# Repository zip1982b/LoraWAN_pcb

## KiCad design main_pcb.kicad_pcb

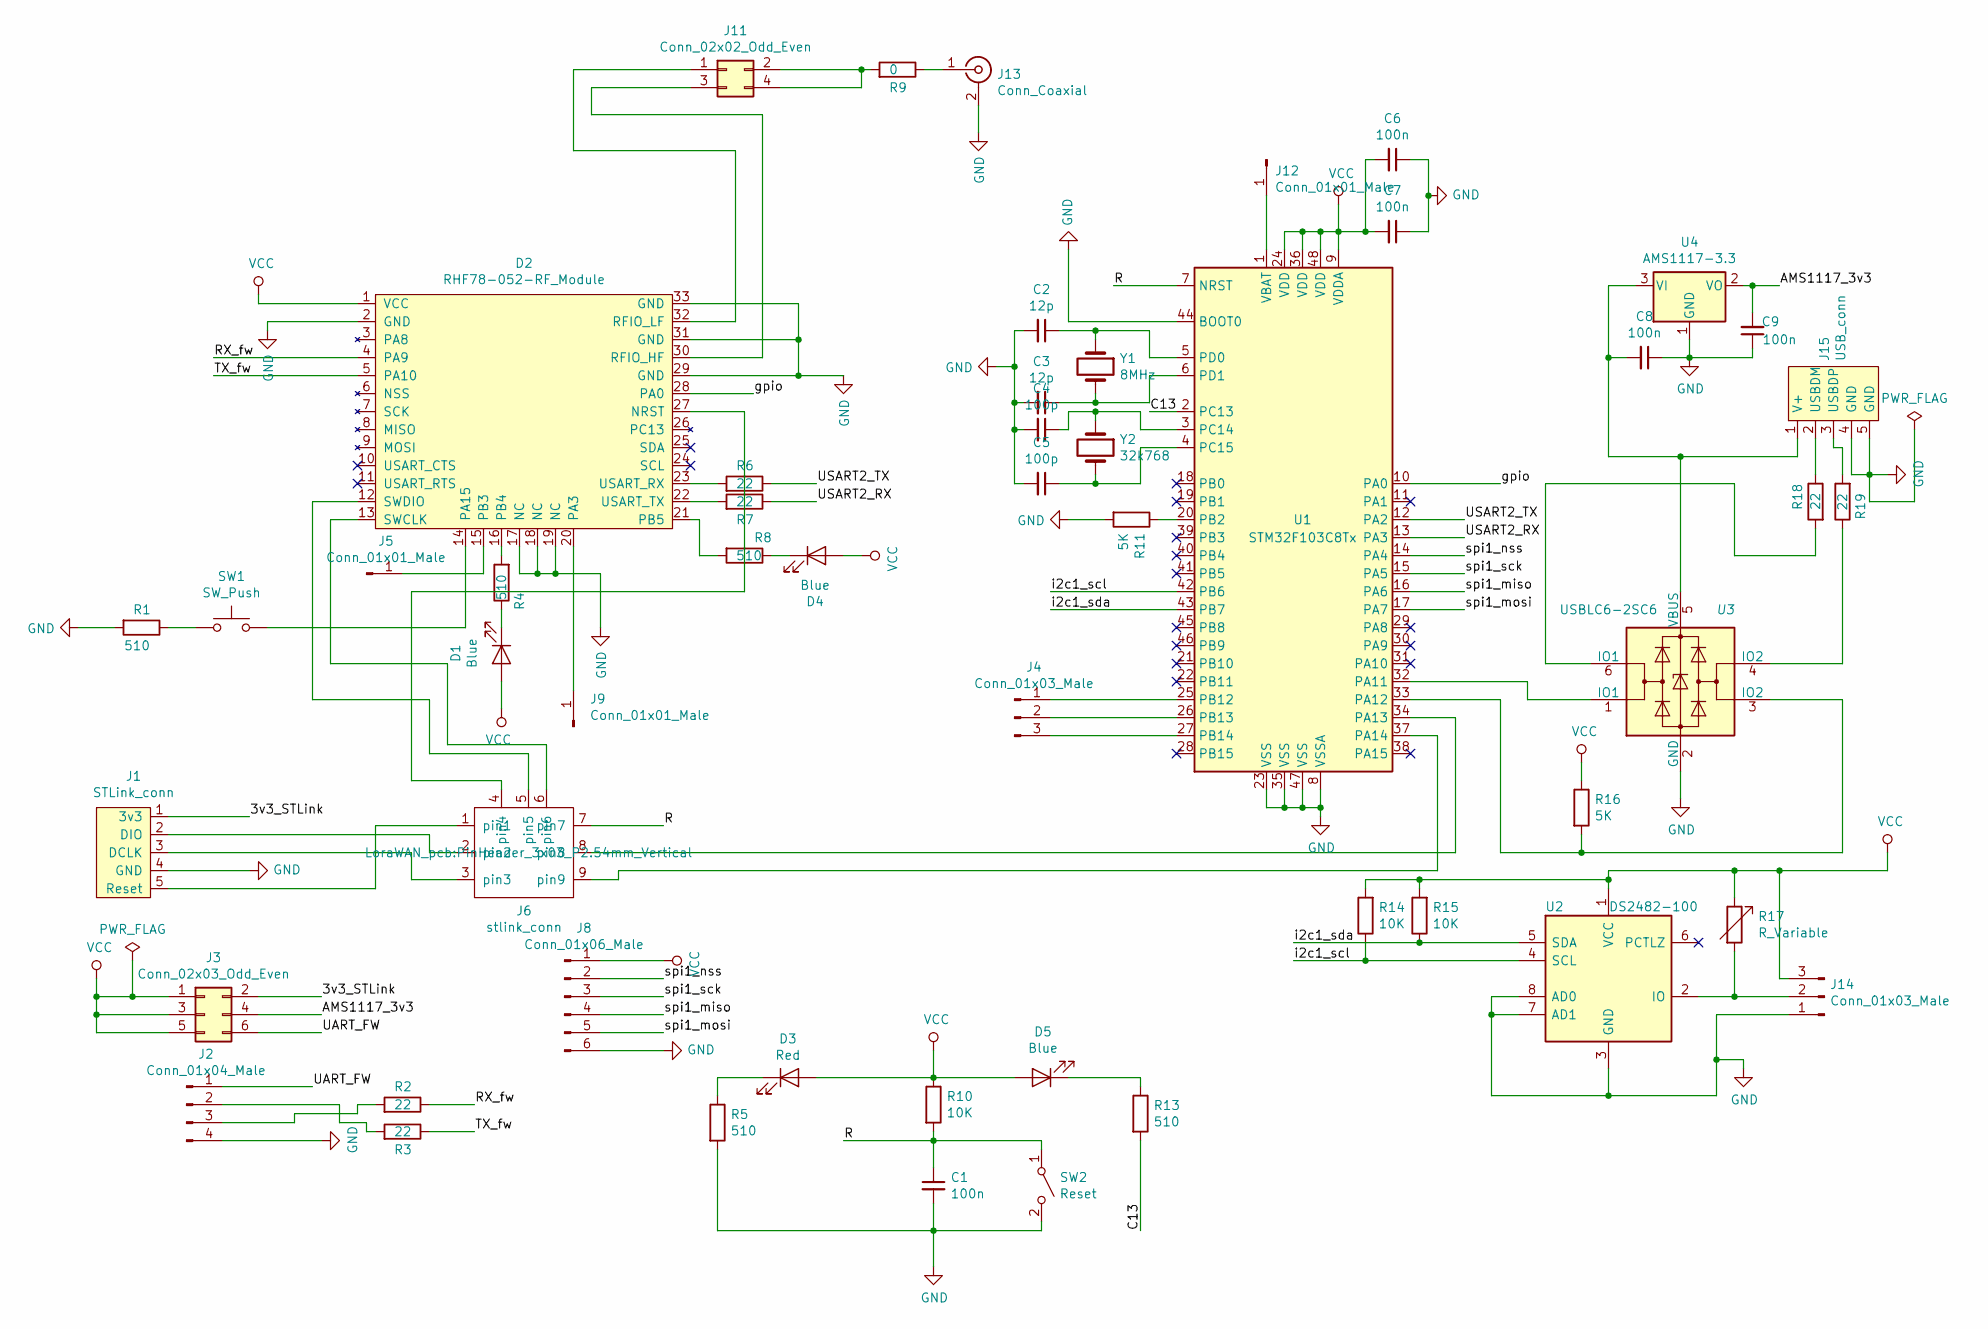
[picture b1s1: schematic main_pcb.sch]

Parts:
C1, C6, C7, C8, C9: 100n; C_0805_HandSoldering
C2, C3: 12p; C_0805_HandSoldering
C4, C5: 100p; C_0805_HandSoldering
D1, D4, D5: Blue; LED_0805_HandSoldering
D2: RHF78-052-RF_Module; RHF78_052
D3: Red; LED_0805_HandSoldering
J1: STLink_conn; Pin_Header_Straight_1x05_Pitch2.54mm
J2: Conn_01x04_Male; Pin_Header_Straight_1x04_Pitch2.54mm
J3: Conn_02x03_Odd_Even; Pin_Header_Straight_2x03_Pitch2.54mm
J4, J14: Conn_01x03_Male; Pin_Header_Straight_1x03_Pitch2.54mm
J5, J9, J12: Conn_01x01_Male; Pin_Header_Straight_1x01_Pitch2.54mm
J6: stlink_conn; PinHeader_3x03_P2.54mm_Vertical
J8: Conn_01x06_Male; Pin_Header_Straight_1x06_Pitch2.54mm
J11: Conn_02x02_Odd_Even; Pin_Header_Straight_2x02_Pitch2.54mm
J13: Conn_Coaxial; U_FL_smd
J15: USB_conn; USB_Micro-B
R1, R4, R5, R8, R13: 510; R_0805_HandSoldering
R2, R3, R6, R7, R18, R19: 22; R_0805_HandSoldering
R9: 0; R_0805_HandSoldering
R10, R14, R15: 10K; R_0805_HandSoldering
R11, R16: 5K; R_0805_HandSoldering
R17: R_Variable; Potentiometer_Trimmer_Bourns_3296W
SW1: SW_Push; SW_SPST_EVQPE1
SW2: Reset; SW_SPST_EVQPE1
U1: STM32F103C8Tx; LQFP-48_7x7mm_Pitch0.5mm
U2: DS2482-100; SOIC-8_3.9x4.9mm_Pitch1.27mm
U3: USBLC6-2SC6; SOT-23-6_Handsoldering
U4: AMS1117-3.3; SOT-223-3_TabPin2
Y1: 8MHz; Crystal_HC18-U_Vertical
Y2: 32k768; Crystal_AT310_d3.0mm_l10.0mm_Vertical

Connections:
/3v3_STLink: J1.1 (3v3), J3.2
/AMS1117_3v3: C9.2, J3.4, U4.2 (VO)
/C13: R13.2, U1.2 (PC13)
/R: C1.1, J6.7, R10.2, SW2.1 (A), U1.7 (NRST)
/RX_fw: D2.4 (PA9), R2.1
/TX_fw: D2.5 (PA10), R3.1
/UART_FW: J2.1, J3.6
/USART2_RX: R7.1, U1.13 (PA3)
/USART2_TX: R6.1, U1.12 (PA2)
/gpio: D2.28 (PA0), U1.10 (PA0)
/i2c1_scl: R14.1, U1.42 (PB6), U2.4 (SCL)
/i2c1_sda: R15.1, U1.43 (PB7), U2.5 (SDA)
/spi1_miso: J8.4, U1.16 (PA6)
/spi1_mosi: J8.5, U1.17 (PA7)
/spi1_nss: J8.2, U1.14 (PA4)
/spi1_sck: J8.3, U1.15 (PA5)
GND: C1.2, C2.2, C3.2, C4.2, C5.2, C6.1, C7.1, C8.1, C9.1, D2.2 (GND), D2.17 (NC), D2.18 (NC), D2.19 (NC), D2.29 (GND), D2.31 (GND), D2.33 (GND), J1.4 (GND), J2.4, J8.6, J13.2 (Ext), J14.1, J15.4 (GND), J15.5 (GND), R1.2, R5.2, R11.2, SW2.2 (B), U1.8 (VSSA), U1.23 (VSS), U1.35 (VSS), U1.44 (BOOT0), U1.47 (VSS), U2.3 (GND), U2.7 (AD1), U2.8 (AD0), U3.2 (GND), U4.1 (GND)
unnamed: C2.1, U1.5 (PD0), Y1.1
unnamed: C3.1, U1.6 (PD1), Y1.2
unnamed: C4.1, U1.3 (PC14), Y2.1
unnamed: C5.1, U1.4 (PC15), Y2.2
unnamed: C8.2, J15.1 (V+), U3.5 (VBUS), U4.3 (VI)
unnamed: D1.1 (K), R4.1
unnamed: D2.12 (SWDIO), J6.5
unnamed: D2.13 (SWCLK), J6.6
unnamed: D2.14 (PA15), SW1.2
unnamed: D2.15 (PB3), J5.1
unnamed: D2.16 (PB4), R4.2
unnamed: D2.20 (PA3), J9.1
unnamed: D2.21 (PB5), R8.2
unnamed: D2.22 (USART_TX), R7.2
unnamed: D2.23 (USART_RX), R6.2
unnamed: D2.27 (NRST), J6.4
unnamed: D2.30 (RFIO_HF), J11.3
unnamed: D2.32 (RFIO_LF), J11.1
unnamed: D3.1 (K), R5.1
unnamed: D4.1 (K), R8.1
unnamed: D5.1 (K), R13.1
unnamed: J1.2 (DIO), J6.2
unnamed: J1.3 (DCLK), J6.3
unnamed: J1.5 (Reset), J6.1
unnamed: J2.2, R3.2
unnamed: J2.3, R2.2
unnamed: J4.1, U1.25 (PB12)
unnamed: J4.2, U1.26 (PB13)
unnamed: J4.3, U1.27 (PB14)
unnamed: J6.8, U1.34 (PA13)
unnamed: J6.9, U1.37 (PA14)
unnamed: J11.2, J11.4, R9.2
unnamed: J12.1, U1.1 (VBAT)
unnamed: J13.1 (In), R9.1
unnamed: J14.2, R17.2, U2.2 (IO)
unnamed: J15.2 (USBDM), R18.1
unnamed: J15.3 (USBDP), R19.2
unnamed: R1.1, SW1.1
unnamed: R11.1, U1.20 (PB2)
unnamed: R16.2, U1.33 (PA12), U3.3 (IO2)
unnamed: R18.2, U3.6 (IO1)
unnamed: R19.1, U3.4 (IO2)
unnamed: U1.32 (PA11), U3.1 (IO1)
VCC: C6.2, C7.2, D1.2 (A), D2.1 (VCC), D3.2 (A), D4.2 (A), D5.2 (A), J3.1, J3.3, J3.5, J8.1, J14.3, R10.1, R14.2, R15.2, R16.1, R17.1, U1.9 (VDDA), U1.24 (VDD), U1.36 (VDD), U1.48 (VDD), U2.1 (VCC)

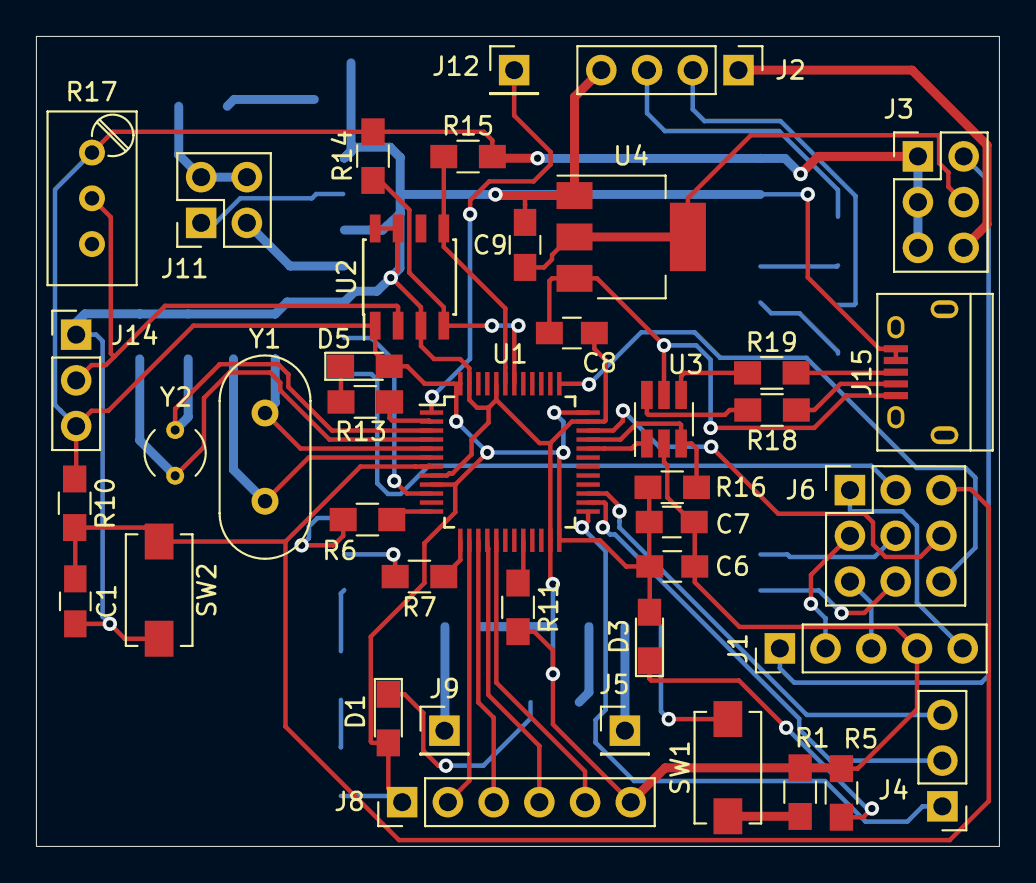
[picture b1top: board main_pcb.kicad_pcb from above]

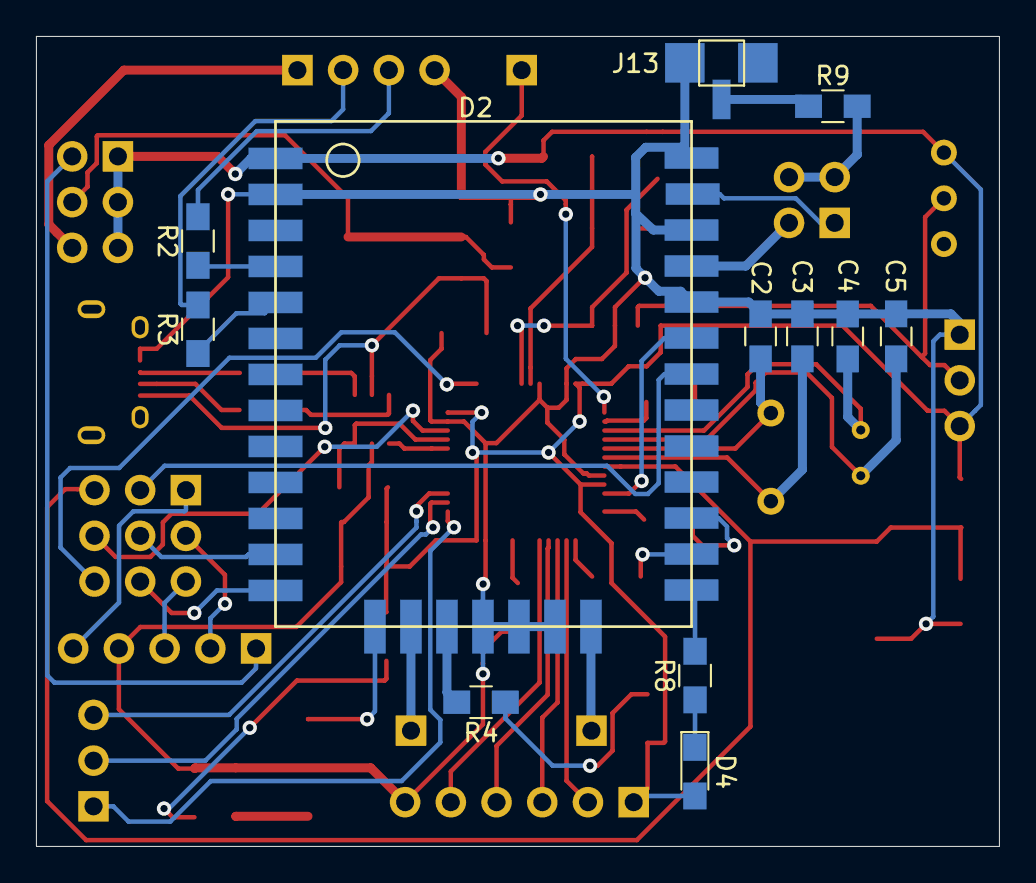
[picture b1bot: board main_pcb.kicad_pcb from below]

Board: 2 copper layers, 53.5 x 45.0 mm, 53 parts (12 on the bottom side), 61 nets.

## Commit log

2020-02-20 add power supply on usb
2020-02-20 add STLink connector
2020-02-22 home pc - add connectors for fw upgrade, power supplay connector, ant connector
2020-02-23 add i2c, spi interface
2020-02-24 add RHF78 footprint
2020-02-27 add footprint
2020-02-29 add key Reset footprint
2020-03-02 pcbnew
2020-03-08 center
2020-03-09 work PC
2020-03-14 stm32 is bootom, rhf78 is top
2020-03-14 add library from home PC
2020-03-17 work pc - pcbnew
2020-03-19 work pc pcbnew
2020-03-21 board trace is finished
2020-04-24 add new pin header 3x3
2020-04-26 pcbnew complited
2020-04-27 create gerber files for manufacturing
